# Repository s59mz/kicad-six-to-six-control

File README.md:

# kicad-six-to-six-control
Arduino control board for Six to Six Splitter/Combiner board

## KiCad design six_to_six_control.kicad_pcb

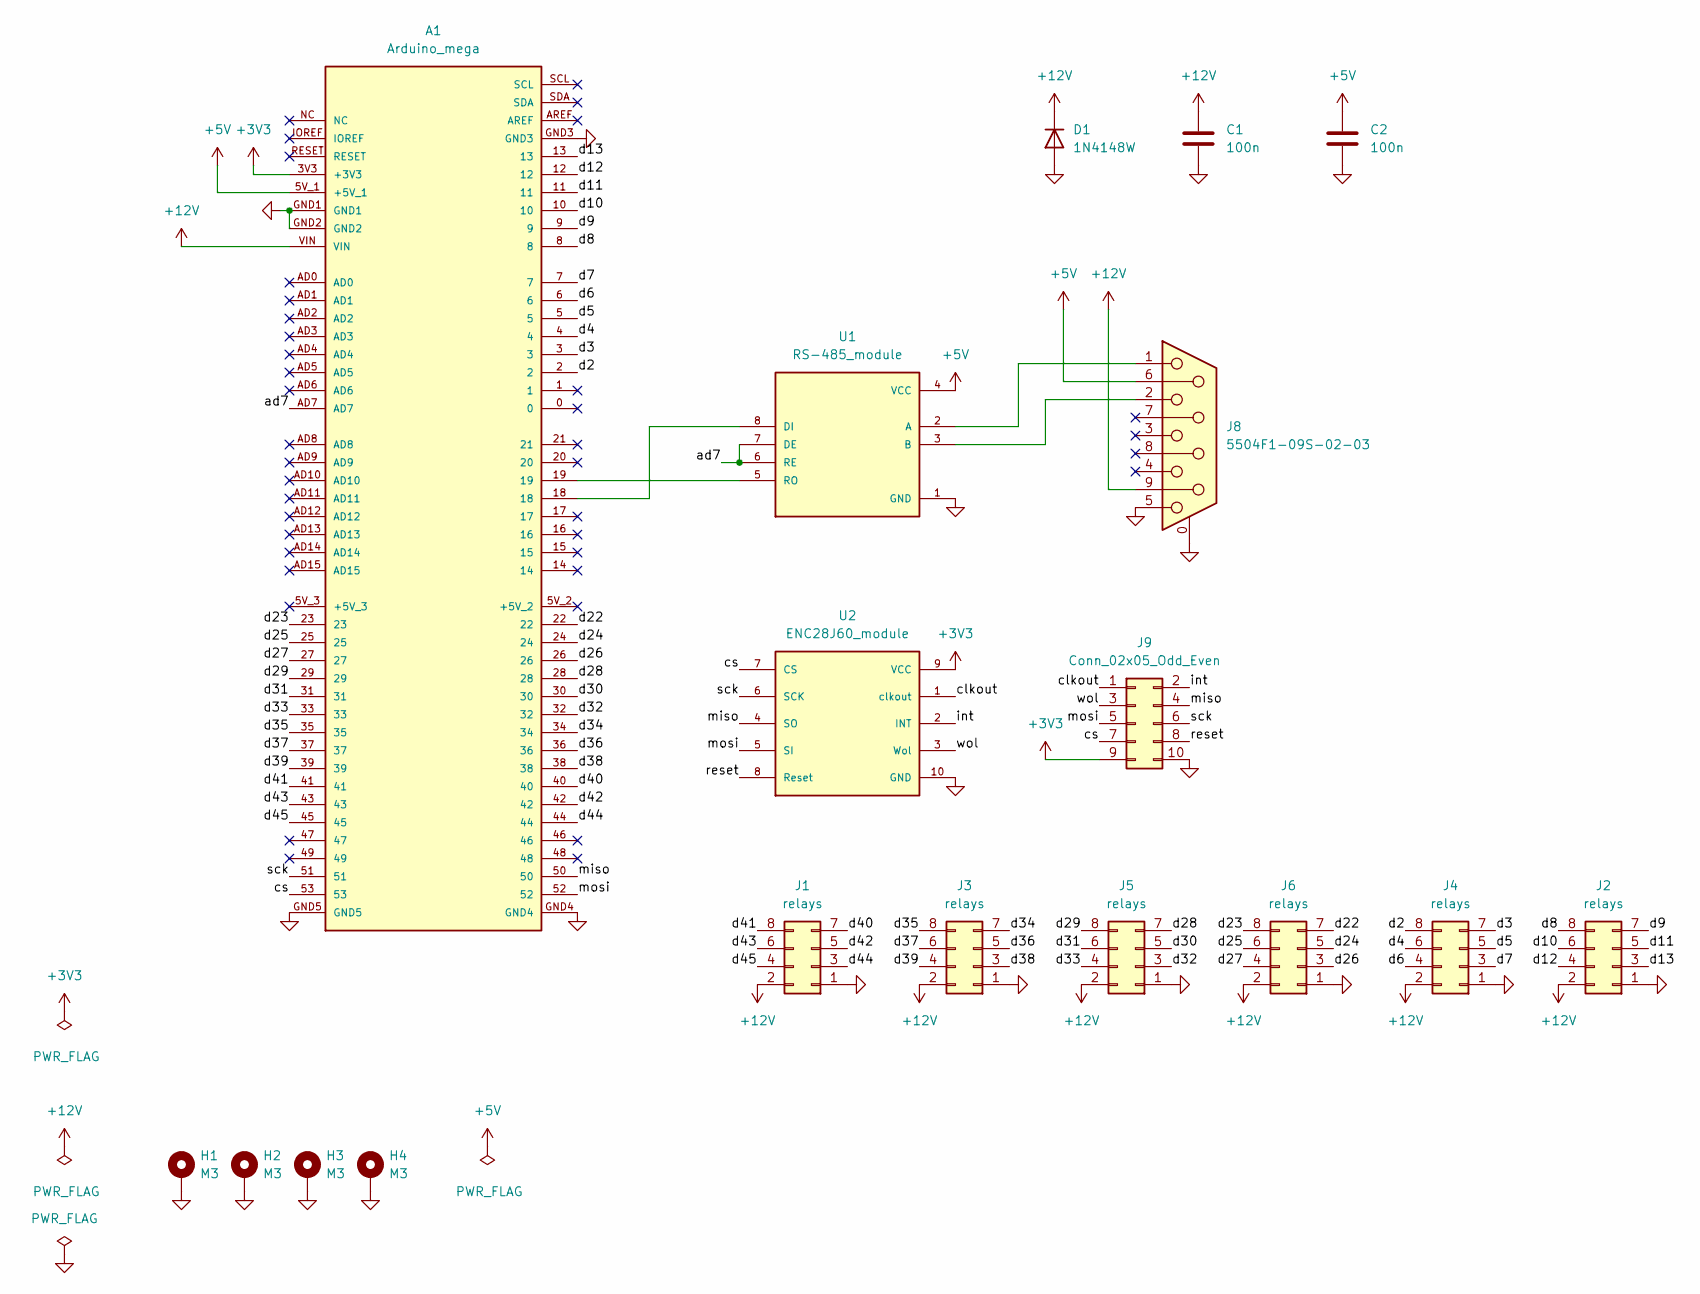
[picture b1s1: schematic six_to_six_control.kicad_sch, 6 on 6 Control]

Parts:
A1: Arduino_mega; ARDUINO_mega
C1, C2: 100n; C_0603_1608Metric_Pad1.08x0.95mm_HandSolder
D1: 1N4148W; D_SOD-123
H1, H2, H3, H4: M3; MountingHole_3.2mm_M3_DIN965_Pad
J1, J2, J3, J4, J5, J6: relays; PinHeader_2x04_P2.54mm_Vertical
J8: 5504F1-09S-02-03; DSUB-9_Female_Horizontal_P2.77x2.84mm_EdgePinOffset7.70mm_H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
J9: Conn_02x05_Odd_Even; PinHeader_2x05_P2.54mm_Vertical
U1: RS-485_module; PARTREV 1r0
U2: ENC28J60_module; PARTREV 1r0

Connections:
+3V3: A1.3V3 (+3V3), J9.9, U2.9 (VCC)
+5V: A1.5V_1 (+5V_1), C2.1, J8.6, U1.4 (VCC)
+12V: A1.VIN, C1.1, D1.1 (K), J1.2, J2.2, J3.2, J4.2, J5.2, J6.2, J8.9; also elsewhere on the board
/ad7: A1.AD7, U1.6 (RE), U1.7 (DE)
/clkout: J9.1, U2.1 (clkout)
/cs: A1.53, J9.7, U2.7 (CS)
/d2: A1.2, J4.8; also elsewhere on the board
/d3: A1.3, J4.7; also elsewhere on the board
/d4: A1.4, J4.6; also elsewhere on the board
/d5: A1.5, J4.5; also elsewhere on the board
/d6: A1.6, J4.4; also elsewhere on the board
/d7: A1.7, J4.3; also elsewhere on the board
/d8: A1.8, J2.8
/d9: A1.9, J2.7
/d10: A1.10, J2.6
/d11: A1.11, J2.5
/d12: A1.12, J2.4
/d13: A1.13, J2.3
/d22: A1.22, J6.7
/d23: A1.23, J6.8
/d24: A1.24, J6.5
/d25: A1.25, J6.6
/d26: A1.26, J6.3
/d27: A1.27, J6.4
/d28: A1.28, J5.7
/d29: A1.29, J5.8
/d30: A1.30, J5.5
/d31: A1.31, J5.6
/d32: A1.32, J5.3
/d33: A1.33, J5.4
/d34: A1.34, J3.7
/d35: A1.35, J3.8
/d36: A1.36, J3.5
/d37: A1.37, J3.6
/d38: A1.38, J3.3
/d39: A1.39, J3.4
/d40: A1.40, J1.7
/d41: A1.41, J1.8
/d42: A1.42, J1.5
/d43: A1.43, J1.6
/d44: A1.44, J1.3
/d45: A1.45, J1.4
/int: J9.2, U2.2 (INT)
/miso: A1.50, J9.4, U2.4 (SO)
/mosi: A1.52, J9.5, U2.5 (SI)
/reset: J9.8, U2.8 (Reset)
/sck: A1.51, J9.6, U2.6 (SCK)
/wol: J9.3, U2.3 (Wol)
GND: A1.GND1, A1.GND2, A1.GND3, A1.GND4, A1.GND5, C1.2, C2.2, D1.2 (A), H1.1, H2.1, H3.1, H4.1, J1.1, J2.1, J3.1, J4.1, J5.1, J6.1, J8.0 (PAD), J8.5, J9.10, U1.1 (GND), U2.10 (GND); also elsewhere on the board
unnamed: A1.18, U1.8 (DI)
unnamed: A1.19, U1.5 (RO)
unnamed: J8.1, U1.2 (A)
unnamed: J8.2, U1.3 (B)

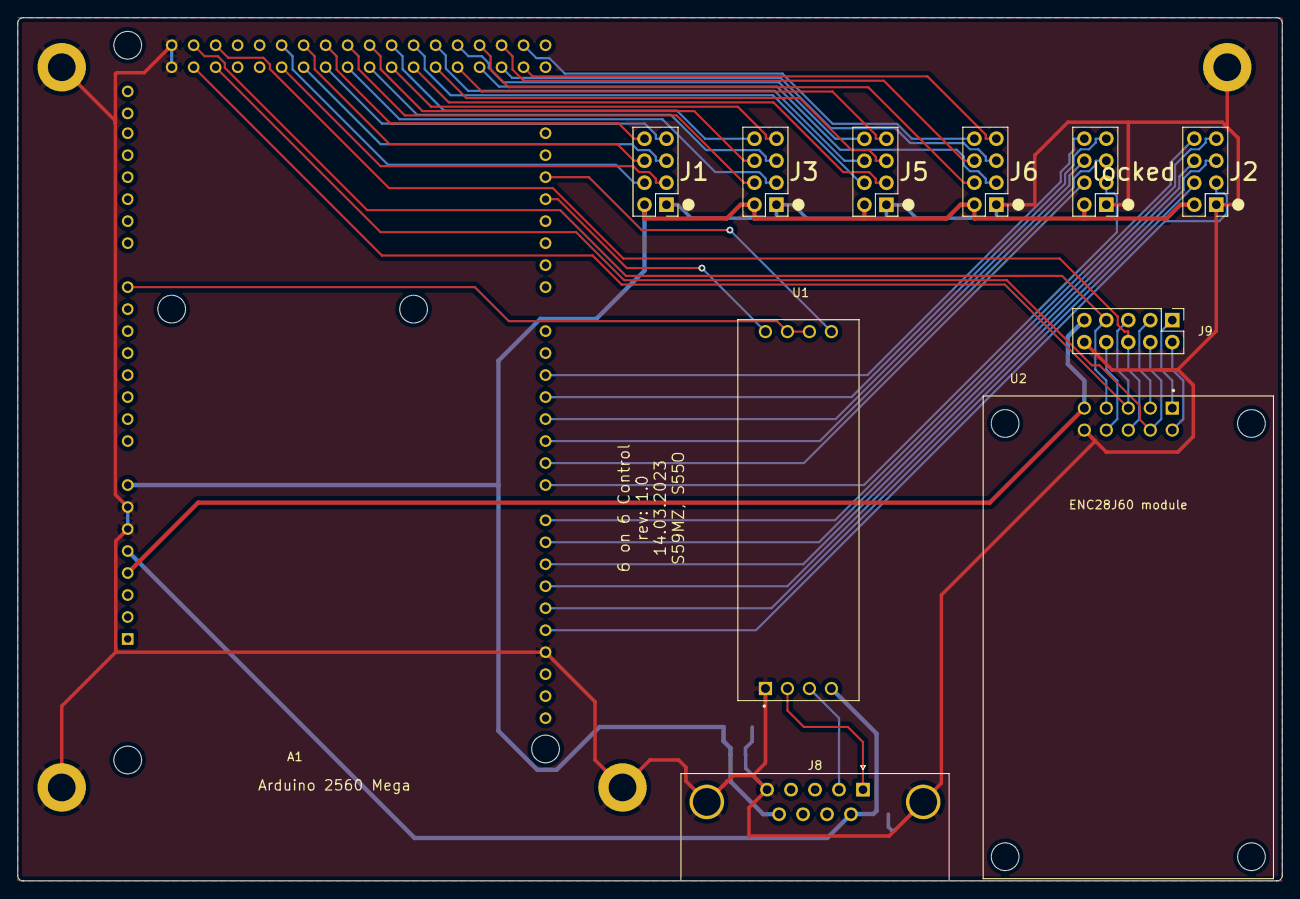
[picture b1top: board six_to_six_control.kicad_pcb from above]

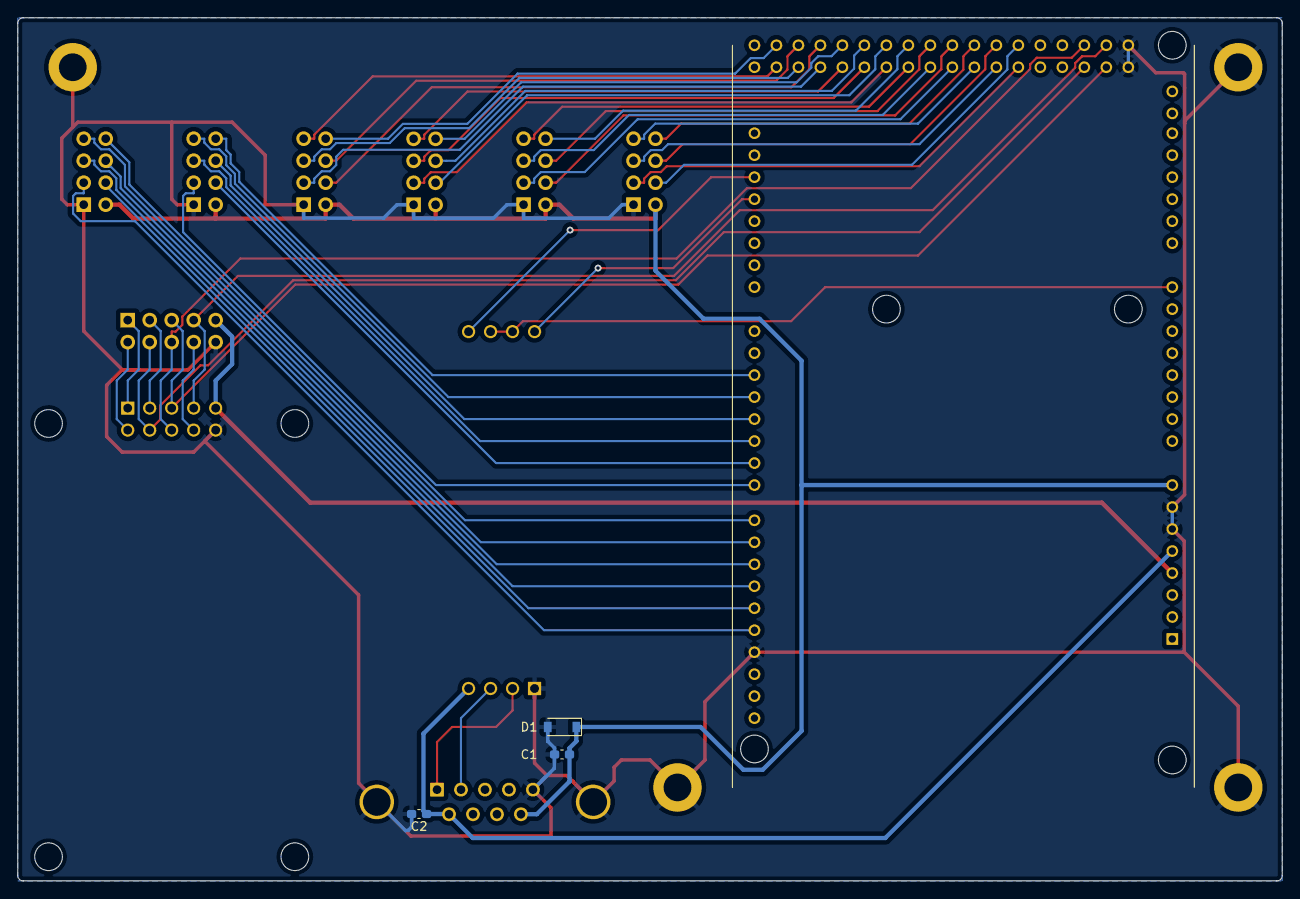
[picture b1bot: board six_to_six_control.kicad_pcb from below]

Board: 2 copper layers, 146.1 x 99.7 mm, 18 parts (4 on the bottom side), 53 nets.

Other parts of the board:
locked: relays; PinHeader_2x04_P2.54mm_Vertical

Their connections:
+12V: locked.2; also elsewhere on the board
/d2: locked.8; also elsewhere on the board
/d3: locked.7; also elsewhere on the board
/d4: locked.6; also elsewhere on the board
/d5: locked.5; also elsewhere on the board
/d6: locked.4; also elsewhere on the board
/d7: locked.3; also elsewhere on the board
GND: locked.1; also elsewhere on the board

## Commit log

2023-03-15 add 3D snapshots
2023-03-28 added db9 and Ethernet module
2023-03-28 fixed db9 layout
2023-03-28 updated jpgs
2023-03-28 reannotate connectors
2023-03-28 added pin1 markers
